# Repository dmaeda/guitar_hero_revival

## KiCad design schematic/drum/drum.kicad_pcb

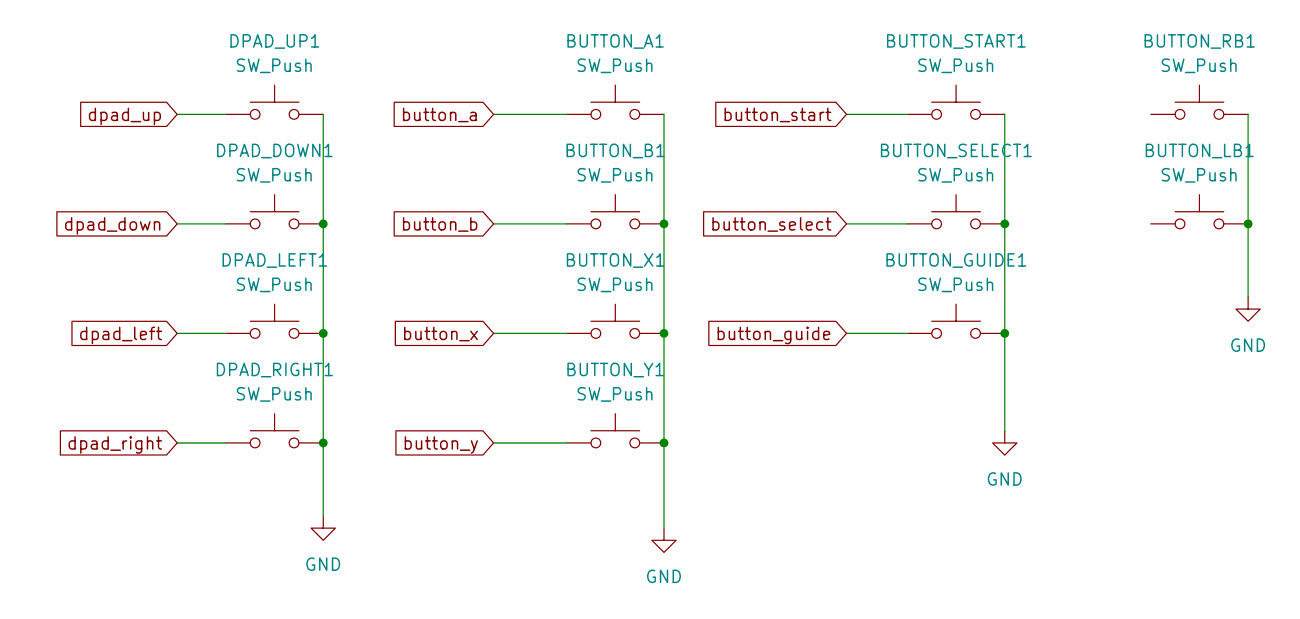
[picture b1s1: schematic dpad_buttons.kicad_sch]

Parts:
BUTTON_A1: SW_Push; SW_SPST_Omron_B3F-50xx
BUTTON_B1: SW_Push; SW_SPST_Omron_B3F-50xx
BUTTON_GUIDE1: SW_Push; SW_SPST_Omron_B3F-50xx
BUTTON_LB1: SW_Push; SW_SPST_Omron_B3F-50xx
BUTTON_RB1: SW_Push; SW_SPST_Omron_B3F-50xx
BUTTON_SELECT1: SW_Push; SW_SPST_Omron_B3F-50xx
BUTTON_START1: SW_Push; SW_SPST_Omron_B3F-50xx
BUTTON_X1: SW_Push; SW_SPST_Omron_B3F-50xx
BUTTON_Y1: SW_Push; SW_SPST_Omron_B3F-50xx
DPAD_DOWN1: SW_Push; SW_SPST_Omron_B3F-50xx
DPAD_LEFT1: SW_Push; SW_SPST_Omron_B3F-50xx
DPAD_RIGHT1: SW_Push; SW_SPST_Omron_B3F-50xx
DPAD_UP1: SW_Push; SW_SPST_Omron_B3F-50xx

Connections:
GND: BUTTON_A1.2, BUTTON_B1.2, BUTTON_GUIDE1.2, BUTTON_LB1.2, BUTTON_RB1.2, BUTTON_SELECT1.2, BUTTON_START1.2, BUTTON_X1.2, BUTTON_Y1.2, DPAD_DOWN1.2, DPAD_LEFT1.2, DPAD_RIGHT1.2, DPAD_UP1.2; also elsewhere on the board
button_a: BUTTON_A1.1; also elsewhere on the board
button_b: BUTTON_B1.1; also elsewhere on the board
button_guide: BUTTON_GUIDE1.1; also elsewhere on the board
button_select: BUTTON_SELECT1.1; also elsewhere on the board
button_start: BUTTON_START1.1; also elsewhere on the board
button_x: BUTTON_X1.1; also elsewhere on the board
button_y: BUTTON_Y1.1; also elsewhere on the board
dpad_down: DPAD_DOWN1.1; also elsewhere on the board
dpad_left: DPAD_LEFT1.1; also elsewhere on the board
dpad_right: DPAD_RIGHT1.1; also elsewhere on the board
dpad_up: DPAD_UP1.1; also elsewhere on the board

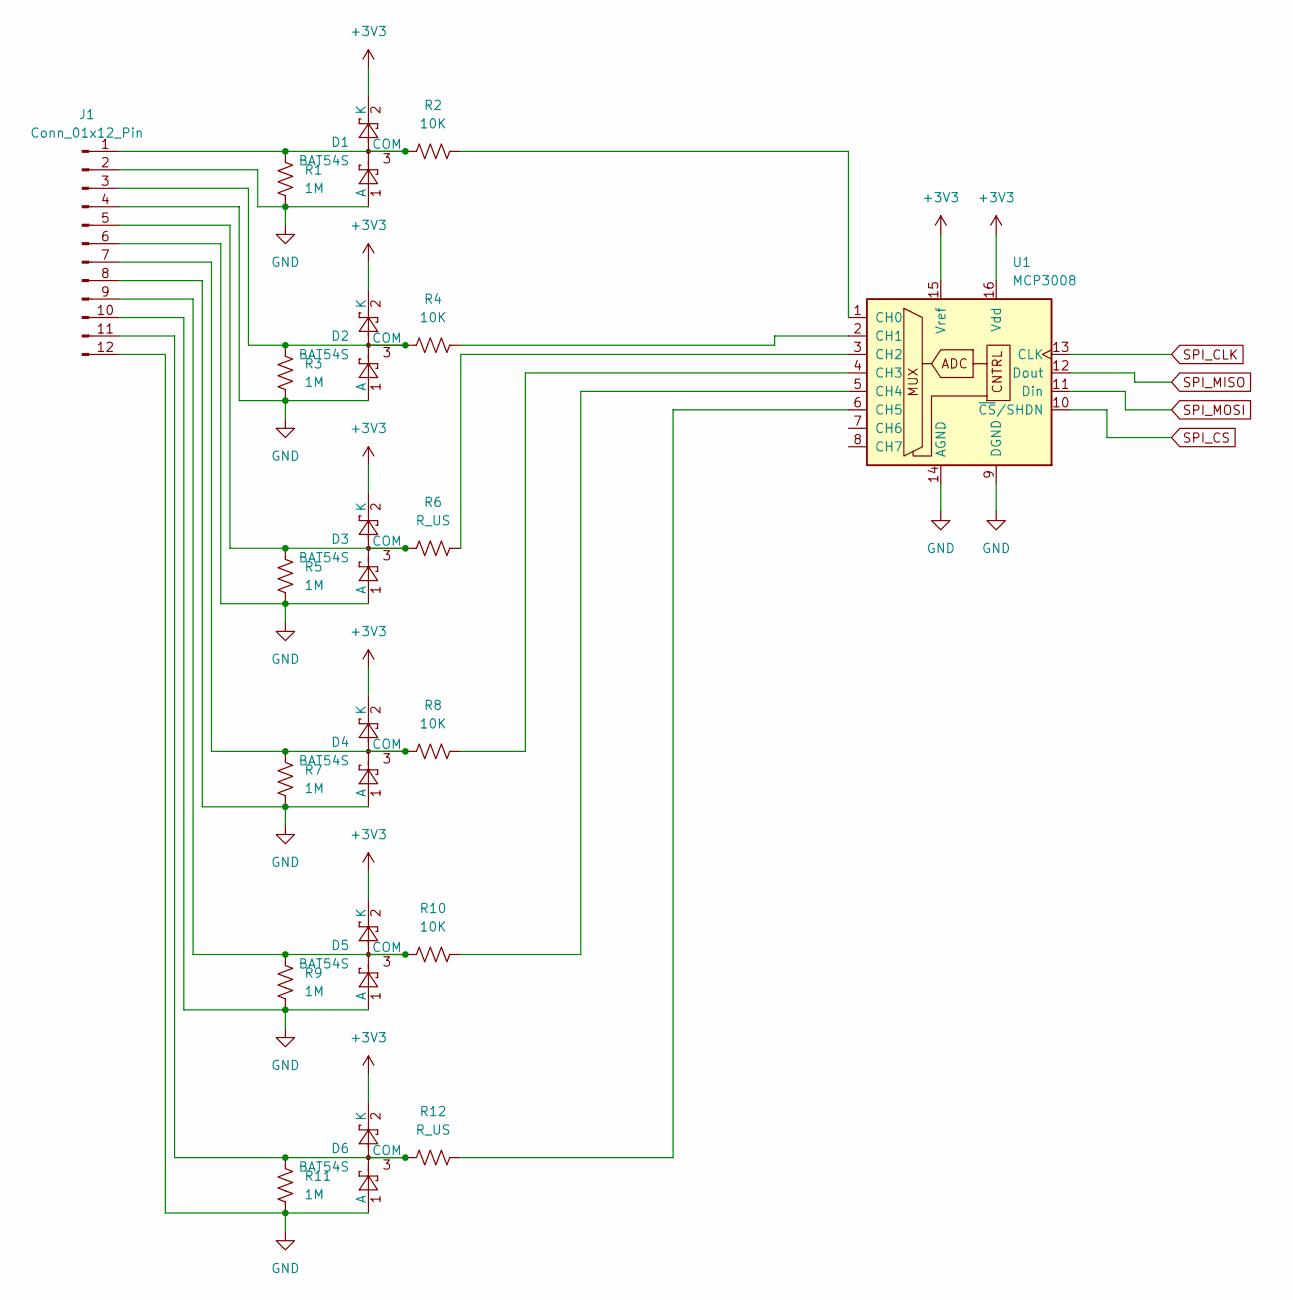
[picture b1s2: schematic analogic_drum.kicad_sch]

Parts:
D1, D2, D3, D4, D5, D6: BAT54S; SOT-23
J1: Conn_01x12_Pin; TerminalBlock_MaiXu_MX126-5.0-12P_1x12_P5.00mm
R1: 1M; R_0805_2012Metric
R2, R4, R8, R10: 10K; R_0805_2012Metric_Pad1.20x1.40mm_HandSolder
R3, R5, R7, R9, R11: 1M; R_0805_2012Metric_Pad1.20x1.40mm_HandSolder
R6, R12: R_US; R_0805_2012Metric_Pad1.20x1.40mm_HandSolder
U1: MCP3008; SOIC-16_3.9x9.9mm_P1.27mm

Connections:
+3V3: D1.2 (K), D2.2 (K), D3.2 (K), D4.2 (K), D5.2 (K), D6.2 (K), U1.15 (Vref), U1.16 (Vdd)
GND: D1.1 (A), D2.1 (A), D3.1 (A), D4.1 (A), D5.1 (A), D6.1 (A), J1.2, J1.4, J1.6, J1.8, J1.10, J1.12, R1.2, R3.2, R5.2, R7.2, R9.2, R11.2, U1.9 (DGND), U1.14 (AGND); also elsewhere on the board
unnamed: D1.3 (COM), J1.1, R1.1, R2.1
unnamed: D2.3 (COM), J1.3, R3.1, R4.1
unnamed: D3.3 (COM), J1.5, R5.1, R6.1
unnamed: D4.3 (COM), J1.7, R7.1, R8.1
unnamed: D5.3 (COM), J1.9, R9.1, R10.1
unnamed: D6.3 (COM), J1.11, R11.1, R12.1
unnamed: R2.2, U1.1 (CH0)
unnamed: R4.2, U1.2 (CH1)
unnamed: R6.2, U1.3 (CH2)
unnamed: R8.2, U1.4 (CH3)
unnamed: R10.2, U1.5 (CH4)
unnamed: R12.2, U1.6 (CH5)
SPI_CLK: U1.13 (CLK); also elsewhere on the board
SPI_CS: U1.10 (~CS/SHDN); also elsewhere on the board
SPI_MISO: U1.12 (Dout); also elsewhere on the board
SPI_MOSI: U1.11 (Din); also elsewhere on the board

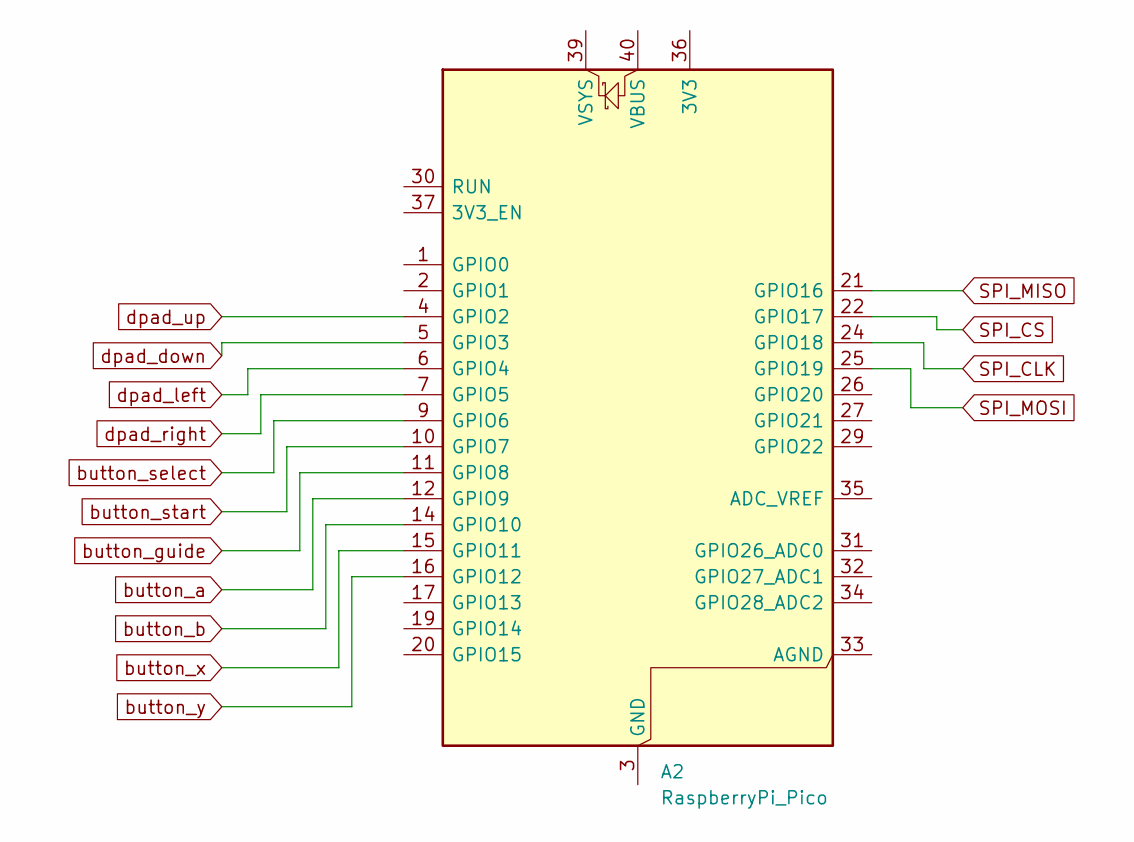
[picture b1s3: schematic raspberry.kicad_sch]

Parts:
A2: RaspberryPi_Pico; RaspberryPi_Pico_Common_THT

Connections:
unnamed: A2.3 (GND), A2.8 (GND), A2.13 (GND), A2.18 (GND), A2.23 (GND), A2.28 (GND), A2.38 (GND)
SPI_CLK: A2.24 (GPIO18); also elsewhere on the board
SPI_CS: A2.22 (GPIO17); also elsewhere on the board
SPI_MISO: A2.21 (GPIO16); also elsewhere on the board
SPI_MOSI: A2.25 (GPIO19); also elsewhere on the board
button_a: A2.12 (GPIO9); also elsewhere on the board
button_b: A2.14 (GPIO10); also elsewhere on the board
button_guide: A2.11 (GPIO8); also elsewhere on the board
button_select: A2.9 (GPIO6); also elsewhere on the board
button_start: A2.10 (GPIO7); also elsewhere on the board
button_x: A2.15 (GPIO11); also elsewhere on the board
button_y: A2.16 (GPIO12); also elsewhere on the board
dpad_down: A2.5 (GPIO3); also elsewhere on the board
dpad_left: A2.6 (GPIO4); also elsewhere on the board
dpad_right: A2.7 (GPIO5); also elsewhere on the board
dpad_up: A2.4 (GPIO2); also elsewhere on the board

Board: 2 copper layers, 34 parts (0 on the bottom side), 30 nets, no tracks yet.
